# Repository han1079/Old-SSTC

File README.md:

# Old-SSTC
Old Solid State Tesla Coil. Audio Modulated

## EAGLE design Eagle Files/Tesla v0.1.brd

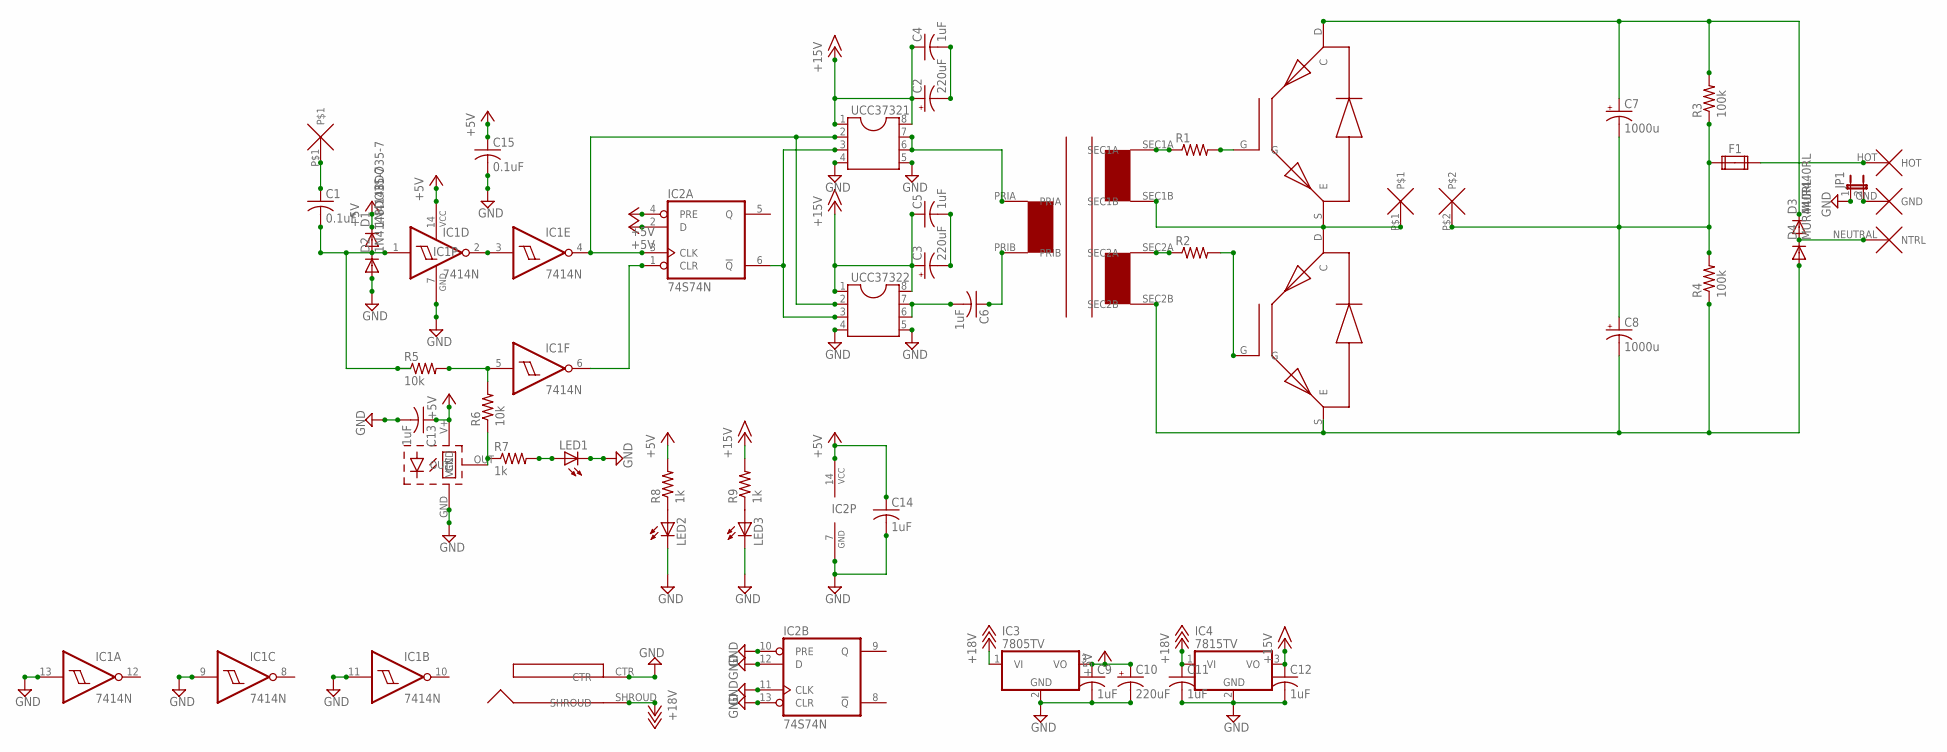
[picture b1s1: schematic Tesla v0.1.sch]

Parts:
C1, C15: 0.1uF; C050-024X044
C2, C3, C10: 220uF; E5-10,5
C4, C5, C6, C9, C11, C12, C13, C14: 1uF; C050-024X044
C7, C8: 1000u; EB25D
D1, D2: 1N4148DO35-7; DO35-7
D3, D4: MUR440RL; C2673
F1: FUSE2P; FUSE1
IC1: 7414N; DIL14
IC2: 74S74N; DIL14
IC3: 7805TV; TO220V
IC4: 7815TV; TO220V
JP1: JP1E; JP1
LED1, LED2, LED3: LED5MM
R1, R2: R-US_0309/V; 0309V
R3, R4: 100k; 0309/10
R5, R6: 10k; 0207/7
R7, R8, R9: 1k; 0207/7
U$1: PJ-037B; DJC0202
U$2: 12AWG_PAD
U$3: GDT
U$4, U$5: FGH40N60SMD; TO247BV
U$6: 2TERMINAL
U$7: IEC; IECPORT
U$8: IF-D95; IFD95
UCC37321, UCC37322: DIL8; DIL08

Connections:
+5V: C9.1, C10.+, C13.1, C14.1, C15.1, D1.C, IC1.14 (VCC), IC2.2 (D), IC2.4 (PRE), IC2.14 (VCC), IC3.3 (VO), R8.2, U$8.V+ (VCC)
+15V: C2.+, C3.+, C4.1, C5.1, C12.1, IC4.3 (VO), R9.2, UCC37321.1, UCC37321.8, UCC37322.1, UCC37322.8
+18V: C11.1, IC3.1 (VI), IC4.1 (VI), U$1.SHROUD
GND: C9.2, C10.-, C11.2, C12.2, C13.2, C14.2, C15.2, D2.A, IC1.7 (GND), IC1.9 (I), IC1.11 (I), IC1.13 (I), IC2.7 (GND), IC2.10 (PRE), IC2.11 (CLK), IC2.12 (D), IC2.13 (CLR), IC3.2 (GND), IC4.2 (GND), JP1.1, LED1.K (C), LED2.K (C), LED3.K (C), U$1.CTR, U$8.GND, UCC37321.4, UCC37321.5, UCC37322.4, UCC37322.5
unnamed: C1.1, U$2.P$1
unnamed: C1.2, D1.A, D2.C, IC1.1 (I), R5.1
unnamed: IC1.4 (O), IC2.3 (CLK), UCC37321.2, UCC37322.2
unnamed: IC1.6 (O), IC2.1 (CLR)
unnamed: IC2.6 (!Q), UCC37321.3, UCC37322.3
unnamed: C2.-, C4.2
unnamed: C3.-, C5.2
unnamed: U$3.PRIA, UCC37321.6, UCC37321.7
unnamed: C6.2, UCC37322.6, UCC37322.7
unnamed: C6.1, U$3.PRIB
unnamed: U$3.SEC1B, U$4.S (E), U$5.D (C), U$6.P$1
unnamed: R1.1, U$3.SEC1A
unnamed: R1.2, U$4.G
unnamed: R2.1, U$3.SEC2A
unnamed: R2.2, U$5.G
unnamed: IC1.5 (I), R5.2, R6.2
unnamed: R6.1, R7.1, U$8.OUT
unnamed: C7.-, C8.+, F1.1A, R3.1, R4.2, U$6.P$2
unnamed: D3.A, D4.C, U$7.NEUTRAL (NTRL)
unnamed: F1.2A, U$7.HOT
unnamed: JP1.2, U$7.GND
unnamed: LED1.A, R7.2
unnamed: LED2.A, R8.1
unnamed: LED3.A, R9.1
unnamed: IC1.2 (O), IC1.3 (I)
V+: C7.+, D3.C, R3.2, U$4.D (C)
V-: C8.-, D4.A, R4.1, U$3.SEC2B, U$5.S (E)

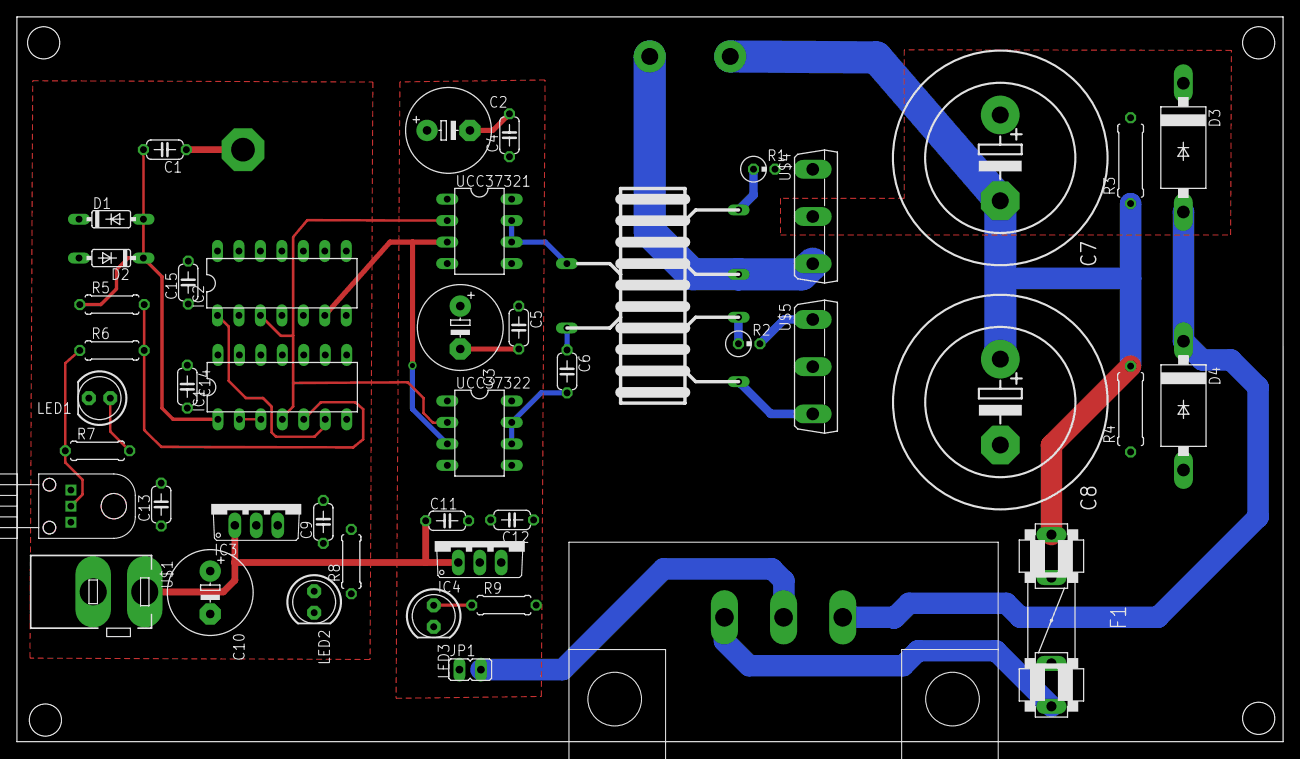
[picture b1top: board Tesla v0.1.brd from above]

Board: 2 copper layers, 149.7 x 85.7 mm, 47 parts (1 on the bottom side), 31 nets.

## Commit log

2017-01-16 Create a
